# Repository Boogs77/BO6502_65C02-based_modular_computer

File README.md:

# BO6502: 65C02-Based Modular Computer System

Technical overview of the **BO6502** core architecture. This system leverages the iconic 6502 instruction set with modern, high-reliability components from Western Design Center, Atmel, and Hitachi, offering a versatile platform for retro-computing enthusiasts.

### 📖 [Read the operation manual](https://github.com/Boogs77/BO6502-manual) · ▶️ [Try it in the browser emulator](https://boogs77.github.io/BO6502-miniVIC-emulator/)

---

## 🧠 Processing Core & System Control

The system is built around a modular 39-pin bus (36 signals + 3 spares) distributed via a robust backplane.

| Module | Type | Status | Description |
| :--- | :--- | :--- | :--- |
| **[CPU Module](https://github.com/Boogs77/BO6502/tree/main/BO6502%20CPU)** |  |  | Central Processing Unit W65C02S. |
| **[Reset & Clock](https://github.com/Boogs77/BO6502/tree/main/BO6502%20RESET)** |  |  | NE555 Reset and switchable clock (2MHz/1MHz/500kHz). |
| **[Backplate](https://github.com/Boogs77/BO6502/tree/main/BO6502%20BACKPLATE)** |  |  | The 39-pin bus backbone with voltage regulation. |
| **[Bridge Connector](https://github.com/Boogs77/BO6502/tree/main/BO6502%20CONNECTOR)** |  |  | Interconnect for daisy-chaining multiple backplates. |

---

## 💾 Memory Map & Storage

The system features a balanced 64KB memory architecture, divided between high-speed static RAM and non-volatile storage.

### [RAM Module](https://github.com/Boogs77/BO6502/tree/main/BO6502%20RAM) ($0000 - $7FFF)
* **Chip**: HITACHI **HM62256LP-12** (32KB SRAM).
* **Status**: 
* **Features**: Revision 02 includes **8 exclusion jumpers** (J-CS0 to J-CS7) to carve out space for I/O modules. Includes JP4 to bypass system clock triggering.
* **PCB**: [RAM_final_rev02](https://github.com/Boogs77/BO6502/blob/main/BO6502%20RAM/gallery/RAM_final_rev02.png?raw=true).

### [ROM Module](https://github.com/Boogs77/BO6502/tree/main/BO6502%20ROM) ($8000 - $FFFF)
* **Chip**: ATMEL **AT28C256** (32KB EEPROM).
* **Status**: 
* **Features**: Equipped with a **ZIF socket** for easy updates. The "Multi" version uses jumpers (J-CS3, CS4, CS5) to disable ROM in specific ranges for advanced peripherals.
* **PCBs**: [Base](https://github.com/Boogs77/BO6502_65C02-based_modular_computer/blob/main/BO6502%20ROM/gallery/ROM_final_rev01.png?raw=true) | [24K Test](https://github.com/Boogs77/BO6502_65C02-based_modular_computer/blob/main/BO6502%20ROM/gallery/ROM24k_final_rev01.png?raw=true) | [Multi-Selection](https://github.com/Boogs77/BO6502_65C02-based_modular_computer/blob/main/BO6502%20ROM/gallery/ROMmulti_final_rev01.png?raw=true).

---

## 🔌 Peripheral & I/O Addressing

Peripheral addressing is managed via **74LS138** decoders to ensure precise memory mapping and avoid bus contention.

| Module | Type | Status | Address | PCB Link |
| :--- | :--- | :--- | :--- | :--- |
| **[VDU Module](https://github.com/Boogs77/BO6502/tree/main/BO6502%20VDU)** |  |  | **$BXXX** | [VDU PCB](https://github.com/Boogs77/BO6502_65C02-based_modular_computer/blob/main/BO6502%20VDU/gallery/VDU_TMS_final_rev01.png?raw=true) |
| **[Serial I/O](https://github.com/Boogs77/BO6502/tree/main/BO6502%20SERIAL)** |  |  | **$CXXX** | [Serial PCB](https://github.com/Boogs77/BO6502_65C02-based_modular_computer/blob/main/BO6502%20SERIAL/gallery/Serial_final_rev03.png?raw=true) |
| **[SD Card](https://github.com/Boogs77/BO6502/tree/main/BO6502%20SDCard)** |  |  | **$D1BX** | [SD Card PCB](https://github.com/Boogs77/BO6502_65C02-based_modular_computer/blob/main/BO6502%20SDCard/gallery/SDcard_final_rev02%20v2.png?raw=true) |
| **[Standalone Keyb](https://github.com/Boogs77/BO6502/tree/main/BO6502%20KEYb)** |  |  | **$D18X** | [Keyboard PCB](https://github.com/Boogs77/BO6502/blob/main/BO6502%20KEYb/gallery/KEYb_final-rev01.png?raw=true) |
| **[Big LCD Module](https://github.com/Boogs77/BO6502/tree/main/BO6502%20BIGLCD)** |  |  | **$D19X** | [Big LCD Module](https://github.com/Boogs77/BO6502/blob/main/BO6502%20BIGLCD/README.md) |
| **[Legacy LCD/Keyb](https://github.com/Boogs77/BO6502/tree/main/BO6502%20LCD_KEYb)** |  |  | **$DXXX** | [Legacy PCB](https://github.com/Boogs77/BO6502/blob/main/BO6502%20LCD_KEYb/gallery/LCD_KEYb_final_rev02.png?raw=true) |
| **[Sound](BO6502%20AUDIO/README.md)** |  |  | **$D1C0** right, **$D1C4** left | [Sound PCB](BO6502%20AUDIO/export/AUDIO_021.png) |

**Stereo sound**: one PCB with one AY-3-8910, built twice; jumpers J-CS0/J-CS1 select the right or left channel. The left board decodes the address and passes the chip select to the right one on **SPARE2** of the backplane. Details in the [Sound module README](BO6502%20AUDIO/README.md).

---

## 📺 Visual Output Tiers

* **Pro**: **TMS9918A** VDU Module with 32KB dedicated RAM. Supports NTSC Composite Out, Sprites, and 16 Colors.
* **Advanced**: **Toshiba T6963** Graphical LCD (160x128 Pixels).
* **Basic**: **Hitachi HD44780U** 16x2 Character LCD.

---

## 🛠 Diagnostic & Testing Tools

| Module | Type | Status | Function | PCB Link |
| :--- | :--- | :--- | :--- | :--- |
| **[Monitor Interface](https://github.com/Boogs77/BO6502/tree/main/BO6502%20MONITOR)** |  |  | Arduino Mega Bus Sniffer (Ben Eater style). | [Monitor PCB](https://github.com/Boogs77/BO6502/blob/main/BO6502%20MONITOR/gallery/MONITOR_final_rev01.png?raw=true) |
| **[LED Test Board](https://github.com/Boogs77/BO6502/tree/main/BO6502%20LED)** |  |  | Visual 16-LED debug for VIA 65C22 ports. | [LED PCB](https://github.com/Boogs77/BO6502/blob/main/BO6502%20LED/gallery/led_final.png?raw=true) |

---

## 📐 Important Technical Notes

### Jumper Configuration for Advanced Modules
When using the latest system modules (VDU, Joystick, SD Card, etc.), the **ROM** and **RAM** modules must be configured to prevent address conflicts:
- **ROM J-CS3/CS4/CS5**: Set to **VCC** to disable ROM in those specific I/O ranges.
- **SD Card Access**: Provides **Raw Data Access** via bit-banged SPI (PA1=MISO, PA2=MOSI, PA3=SCK, PA4=CS).

## 🎬 Videos

Explanatory videos (about five minutes), in Italian and English, with subtitles. Click a picture to watch the video on YouTube.

**The BO6502 modular computer, module by module**

<table><tr>
<td align="center"><br>Italiano</td>
<td align="center"><br>English</td>
</tr></table>

**The BO6502 sound board and how to program the AY-3-8910**

<table><tr>
<td align="center"><br>Italiano</td>
<td align="center"><br>English</td>
</tr></table>

## 📖 Operation Manual

The **[BO6502 Operation Manual](https://github.com/Boogs77/BO6502-manual)**, in the style of the 1976 Apple-1 manual, describes the system board by board: the 39-pin bus pinout, memory and device maps, address decoding, every module with its jumpers, the schematics and bills of materials, every chip register, the BIOS, WozMon and Microsoft BASIC.

| Language | Screen edition | Print edition |
| :--- | :--- | :--- |
| English | [BO6502_Manual_EN.pdf](https://github.com/Boogs77/BO6502-manual/blob/main/BO6502_Manual_EN.pdf) | [BO6502_Manual_EN_print.pdf](https://github.com/Boogs77/BO6502-manual/blob/main/BO6502_Manual_EN_print.pdf) |
| Italian | [BO6502_Manual_IT.pdf](https://github.com/Boogs77/BO6502-manual/blob/main/BO6502_Manual_IT.pdf) | [BO6502_Manual_IT_print.pdf](https://github.com/Boogs77/BO6502-manual/blob/main/BO6502_Manual_IT_print.pdf) |

## 📜 License

The project is open hardware. You are free to build, use, study, modify and sell it, as long as you credit the author.

| Content | License |
| :--- | :--- |
| **Hardware**: schematics, PCB files, bill of materials | [CERN-OHL-P v2](LICENSE) (permissive) |
| **Documentation and images**: README, photos, renders | [CC BY 4.0](LICENSE-docs) |

Copyright (c) 2026 Boogs77. Please keep the credit "by Boogs77" and a link to this repository in your copies and derivatives.

Third-party code in the firmware (for example Microsoft BASIC and WozMon) is not covered by these licenses.

---

## 🏭 Gerber files

Ready for PCB manufacturing (2 layers, drill file included). The drill hits of each file have been checked against its EAGLE board.

| Gerber (ZIP) | Exported from |
| :--- | :--- |
| [`BO6502_AUDIO_gerber.zip`](BO6502%20AUDIO/export/BO6502_AUDIO_gerber.zip) | `AUDIO_final_rev03.brd` |
| [`BO6502_backplate5V_gerber.zip`](BO6502%20BACKPLATE/export/BO6502_backplate5V_gerber.zip) | `backplate5V_final_rev01.brd` |
| [`BO6502_backplate_gerber.zip`](BO6502%20BACKPLATE/export/BO6502_backplate_gerber.zip) | `backplate_final_rev02.brd` |
| [`BO6502-BigLCD_final_gerber.zip`](BO6502%20BIGLCD/export/BO6502-BigLCD_final_gerber.zip) | `BigLCD_final_rev02.brd` |
| [`BO6502_connector_gerber.zip`](BO6502%20CONNECTOR/export/BO6502_connector_gerber.zip) | `connector_final_rev01.brd` |
| [`BO6502_CPU_gerber.zip`](BO6502%20CPU/export/BO6502_CPU_gerber.zip) | `CPU_final_rev02.brd` |
| [`Joystick_final_rev02_gerber.zip`](BO6502%20JOYSTICK/export/Joystick_final_rev02_gerber.zip) | `Joystick_final_rev02.brd` |
| [`KEYb_final_gerber.zip`](BO6502%20KEYb/export/KEYb_final_gerber.zip) | `KEYb_final-rev01.brd` |
| [`BO6502_LCD-KEYb_gerber.zip`](BO6502%20LCD_KEYb/export/BO6502_LCD-KEYb_gerber.zip) | `LCD_KEYb_final_rev02.brd` |
| [`BO6502_LED_gerber.zip`](BO6502%20LED/export/BO6502_LED_gerber.zip) | `led_final.brd` |
| [`BO6502_MONITOR_gerber.zip`](BO6502%20MONITOR/export/BO6502_MONITOR_gerber.zip) | `MONITOR_final_rev01.brd` |
| [`BO6502-RAM_gerber.zip`](BO6502%20RAM/export/BO6502-RAM_gerber.zip) | `RAM_final_rev02.brd` |
| [`BO6502_reset_gerber.zip`](BO6502%20RESET/export/BO6502_reset_gerber.zip) | `reset_final_rev01.brd` |
| [`BO6502_ROM24K_gerber.zip`](BO6502%20ROM/export/BO6502_ROM24K_gerber.zip) | `ROM24k_final_rev01.brd` |
| [`BO6502_ROM_gerber.zip`](BO6502%20ROM/export/BO6502_ROM_gerber.zip) | `ROM_final_rev01.brd` |
| [`BO6502_ROMMULTI_gerber.zip`](BO6502%20ROM/export/BO6502_ROMMULTI_gerber.zip) | `ROMmulti_final_rev01.brd` |
| [`BO6502_SDCARD_gerber.zip`](BO6502%20SDCard/export/BO6502_SDCARD_gerber.zip) | `SDcard_final_rev02.brd` |
| [`BO6502_serial_gerber.zip`](BO6502%20SERIAL/export/BO6502_serial_gerber.zip) | `Serial_final_rev03.brd` |
| [`VDU_TMS_gerber.zip`](BO6502%20VDU/export/VDU_TMS_gerber.zip) | `VDU_TMS_final_rev01.brd` |

---
© 2026 Boogs77 | BO6502 Project - Technical Documentation.

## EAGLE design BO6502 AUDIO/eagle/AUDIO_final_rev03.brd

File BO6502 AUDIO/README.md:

# BO6502 Sound Module

Sound board for the BO6502 system, built around one **General Instrument AY-3-8910** Programmable Sound Generator (3 voices, noise, envelope).

**One PCB, two channels.** The same board is built twice and the jumpers decide whether it is the **right** or the **left** channel. The idea was to separate the two channels and see whether a single printed design could serve both, saving on PCB production.

| Right channel (red RCA) | Left channel (white RCA) |
| :---: | :---: |
|  |  |

On the right board IC1, IC2 and IC3 are not fitted.

---

## 🔊 Stereo with two boards

| Channel | J-CS0 | J-CS1 | Latch address | Write data | Read data |
| :--- | :---: | :---: | :---: | :---: | :---: |
| **Right** | 2-3 | 2-3 | `$D1C0` | `$D1C1` | `$D1C2` |
| **Left** | 1-2 | 1-2 | `$D1C4` | `$D1C5` | `$D1C6` |

J-CS0 and J-CS1 must always be set to the same channel.

### Shared chip select on SPARE2

The address is decoded **on the left board only**. The resulting chip select (`~CS`, active low) travels to the right board on **SPARE2** (pin 38) of the 39-pin bus.

| Part | Left board | Right board |
| :--- | :---: | :---: |
| IC1, IC2, IC3 (address decoder) | fitted | **not fitted** |
| IC4, IC5 (bus control), IC7 (AY-3-8910) | fitted | fitted |

> [!IMPORTANT]
> * Fit IC1-IC3 on the left board only: otherwise two outputs drive the same SPARE2 line.
> * The right board does not work without the left one on the same bus.
> * Do not use SPARE2 for anything else while the sound boards are plugged in.

---

## 🕹️ Address decoding and bus control

* **IC1, IC2, IC3** (74AC138) decode the range `$D1C0-$D1CF` and generate `~CS`. **A3 is not decoded**, so `$D1C8-$D1CF` repeats `$D1C0-$D1C7`.
* **IC4** (74AC138) combines `~CS`, `A0`, `A1`, `R/~W` and `A2` (channel, through J-CS0 and J-CS1).
* **IC5** (74HCT00) turns the IC4 outputs into `BDIR` and `BC1`. `BC2` is tied to VCC.
* The AY clock is **PHI0** from the bus.

| Offset (from the channel base) | Access | BDIR | BC1 | Operation |
| :---: | :---: | :---: | :---: | :--- |
| +0 | write | 1 | 1 | latch the register number |
| +1 | write | 1 | 0 | write the register |
| +2 | read | 0 | 1 | read the register |

---

## 🎚️ Output and optional amplifier

**Both final boards:** J-CS2 on 1-2, JP1 open (no amplifier), JP2 closed (470 Ω resistor out).

The three AY channels are mixed (R2, R3, R4) to a single **RCA** socket, one per board. An **LM386** amplifier stage was added in case it is needed. The two final boards do not use it.

| Jumper | Setting | Effect |
| :--- | :--- | :--- |
| **J-CS2** | 1-2 | direct output to the RCA socket |
| **J-CS2** | 2-3 | amplified output to the RCA socket |
| **JP1** (AMPLI ON) | closed | feeds the LM386 input |
| **JP2** (R470 OFF) | closed | bypasses the 470 Ω series resistor (R5) of the direct output |
| **JP2** (R470 OFF) | open | R5 in series with the direct output |

The extra jumpers are there to try other configurations according to needs.

---

## 📐 Technical specifications

| Specification | Detail |
| :--- | :--- |
| **Sound chip** | 1x AY-3-8910 per board |
| **Logic** | 4x 74AC138, 1x 74HCT00 (right board: 1x 74AC138, 1x 74HCT00) |
| **Amplifier** | 1x LM386 (optional) |
| **Output** | 1x RCA per board |
| **Bus connector** | 39-pin (36 active + 3 spare, SPARE2 used for `~CS`) |

---

## 📁 Files

| File | Content |
| :--- | :--- |
| [`eagle/AUDIO_final_rev03.sch`](eagle/AUDIO_final_rev03.sch), [`.brd`](eagle/AUDIO_final_rev03.brd) | EAGLE schematic and board, **rev. 03** (final) |
| [`export/BO6502-AUDIO_021.pdf`](export/BO6502-AUDIO_021.pdf) | schematic sheet of rev. 03 (internal file number 021) |
| `eagle/AUDIO_005.*`, `export/BO6502-AUDIO_005.pdf` | superseded version with two AY chips on one board |

---

## 🎬 Video

How the board works and how to program it (4:40, with subtitles). Click a picture to watch it on YouTube.

<table><tr>
<td align="center"><br>Italiano</td>
<td align="center"><br>English</td>
</tr></table>

---

## 📂 Related modules
* 🏗️ **[Backplate System](../BO6502%20BACKPLATE/README.md)**: main bus backbone.
* 🧠 **[CPU Module](../BO6502%20CPU/README.md)**: system processing unit.

---

## 🏭 Gerber files

Ready for PCB manufacturing (2 layers, drill file included). The drill hits of each file have been checked against its EAGLE board.

| Gerber (ZIP) | Exported from |
| :--- | :--- |
| [`BO6502_AUDIO_gerber.zip`](export/BO6502_AUDIO_gerber.zip) | `AUDIO_final_rev03.brd` |

---
© 2026 Boogs77 | Engineered for the 6502 enthusiast.

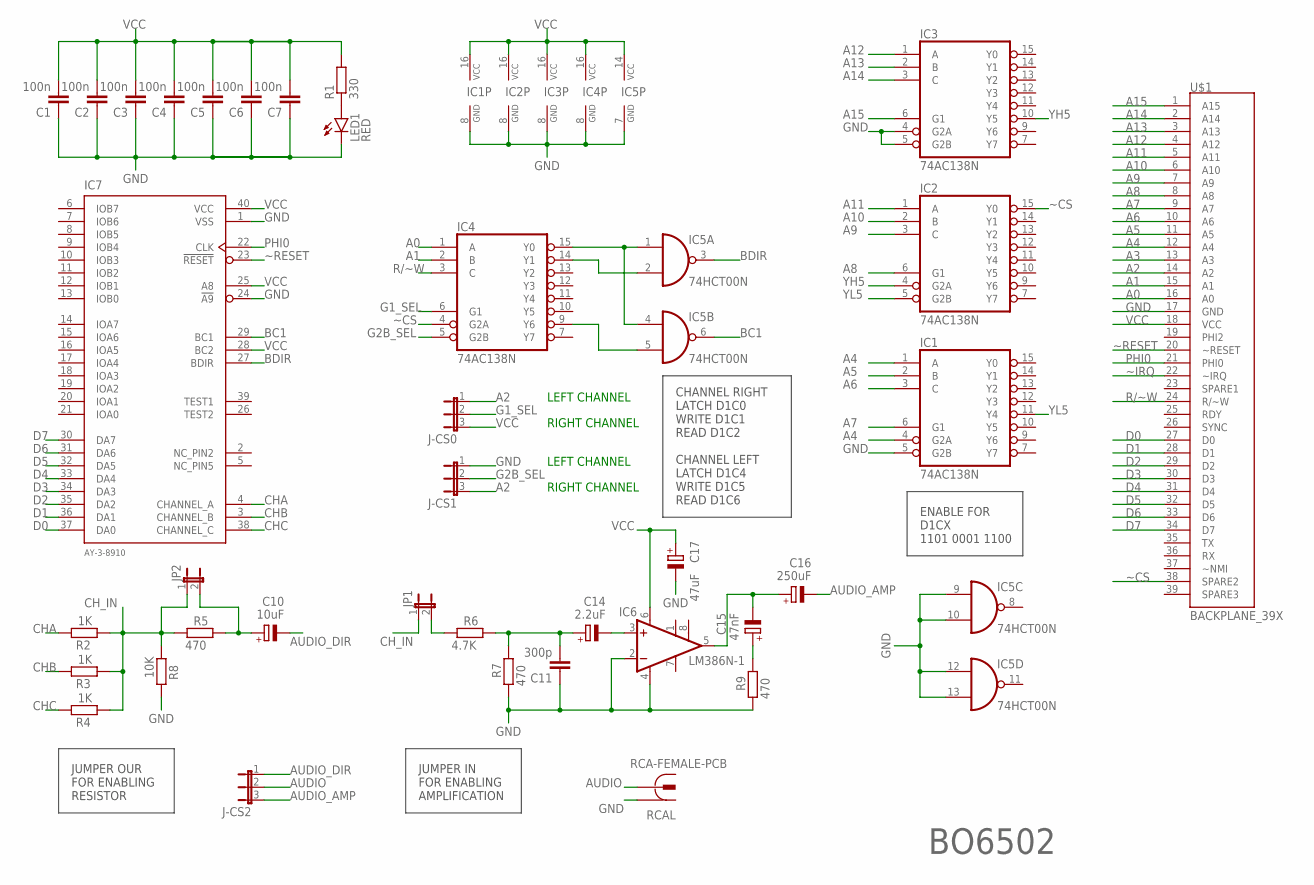
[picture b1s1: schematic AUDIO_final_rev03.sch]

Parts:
C1, C2, C3, C4, C5, C6, C7: 100n; C025-025X050
C10: 10uF; B45181A
C11: 300p; C025-025X050
C14: 2.2uF; B45181A
C15: 47nF; B45181A
C16: 250uF; B45181A
C17: 47uF; B45181A
IC1, IC2, IC3, IC4: 74AC138N; DIL16
IC5: 74HCT00N; DIL14
IC6: LM386N-1; DIL08
IC7: AY-3-8910; DIL40
J-CS0: J-CS0; JP2
J-CS1: J-CS1; JP2
J-CS2: J-CS2; JP2
JP1, JP2: 2PIN; JP1
LED1: RED; LED5MM
R1: 330; 0207/10
R2, R3, R4: 1K; 0207/10
R5, R7, R9: 470; 0207/10
R6: 4.7K; 0207/10
R8: 10K; 0207/10
RCAL: RCA-FEMALE-PCB
U$1: BACKPLANE_39X; BP_39X

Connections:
A0: IC4.1 (A), U$1.16 (A0)
A1: IC4.2 (B), U$1.15 (A1)
A2: J-CS0.1, J-CS1.3, U$1.14 (A2)
A3: U$1.13 (A3)
A4: IC1.1 (A), IC1.4 (G2A), U$1.12 (A4)
A5: IC1.2 (B), U$1.11 (A5)
A6: IC1.3 (C), U$1.10 (A6)
A7: IC1.6 (G1), U$1.9 (A7)
A8: IC2.6 (G1), U$1.8 (A8)
A9: IC2.3 (C), U$1.7 (A9)
A10: IC2.2 (B), U$1.6 (A10)
A11: IC2.1 (A), U$1.5 (A11)
A12: IC3.1 (A), U$1.4 (A12)
A13: IC3.2 (B), U$1.3 (A13)
A14: IC3.3 (C), U$1.2 (A14)
A15: IC3.6 (G1), U$1.1 (A15)
AUDIO: J-CS2.2, RCAL.2@1 (2), RCAL.2@2 (2)
AUDIO_AMP: C16.-, J-CS2.3
AUDIO_DIR: C10.-, J-CS2.1
BC1: IC5.6 (O), IC7.29 (BC1)
BDIR: IC5.3 (O), IC7.27 (BDIR)
CHA: IC7.4 (CHANNEL_A), R2.1
CHB: IC7.3 (CHANNEL_B), R3.1
CHC: IC7.38 (CHANNEL_C), R4.1
CH_IN: JP1.1, JP2.1, R2.2, R3.2, R4.2, R5.2, R8.2
D0: IC7.37 (DA0), U$1.27 (D0)
D1: IC7.36 (DA1), U$1.28 (D1)
D2: IC7.35 (DA2), U$1.29 (D2)
D3: IC7.34 (DA3), U$1.30 (D3)
D4: IC7.33 (DA4), U$1.31 (D4)
D5: IC7.32 (DA5), U$1.32 (D5)
D6: IC7.31 (DA6), U$1.33 (D6)
D7: IC7.30 (DA7), U$1.34 (D7)
G1_SEL: IC4.6 (G1), J-CS0.2
G2B_SEL: IC4.5 (G2B), J-CS1.2
GND: C1.1, C2.1, C3.1, C4.1, C5.1, C6.1, C7.1, C11.1, C17.-, IC1.5 (G2B), IC1.8 (GND), IC2.8 (GND), IC3.4 (G2A), IC3.5 (G2B), IC3.8 (GND), IC4.8 (GND), IC5.7 (GND), IC5.9 (I0), IC5.10 (I1), IC5.12 (I0), IC5.13 (I1), IC6.2 (-IN), IC6.4 (GND), IC7.1 (VSS), IC7.24 (!A9), J-CS1.1, LED1.K (C), R7.2, R8.1, R9.2, RCAL.1, U$1.17 (GND)
unnamed: JP1.2, R6.2
unnamed: IC4.15 (Y0), IC5.1 (I0), IC5.4 (I0)
unnamed: C14.-, IC6.3 (+IN)
unnamed: IC4.14 (Y1), IC5.2 (I1)
unnamed: LED1.A, R1.1
unnamed: C10.+, JP2.2, R5.1
unnamed: IC4.9 (Y6), IC5.5 (I1)
unnamed: C11.2, C14.+, R6.1, R7.1
unnamed: C15.-, C16.+, IC6.5 (OUT)
unnamed: C15.+, R9.1
PHI0: IC7.22 (CLK), U$1.21 (PHI0)
R/~W: IC4.3 (C), U$1.24 (R/~W)
VCC: C1.2, C2.2, C3.2, C4.2, C5.2, C6.2, C7.2, C17.+, IC1.16 (VCC), IC2.16 (VCC), IC3.16 (VCC), IC4.16 (VCC), IC5.14 (VCC), IC6.6 (VS), IC7.25 (A8), IC7.28 (BC2), IC7.40 (VCC), J-CS0.3, R1.2, U$1.18 (VCC)
YH5: IC2.4 (G2A), IC3.10 (Y5)
YL5: IC1.11 (Y4), IC2.5 (G2B)
~CS: IC2.15 (Y0), IC4.4 (G2A), U$1.38 (SPARE2)
~IRQ: U$1.22 (~IRQ)
~RESET: IC7.23 (!RESET), U$1.20 (~RESET)

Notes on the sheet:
BO6502
ENABLE FOR D1CX 1101 0001 1100
LEFT CHANNEL
RIGHT CHANNEL
JUMPER OUR FOR ENABLING RESISTOR
JUMPER IN FOR ENABLING AMPLIFICATION
CHANNEL RIGHT LATCH D1C0 WRITE D1C1 READ D1C2 CHANNEL LEFT LATCH D1C4 WRITE D1C5 READ D1C6

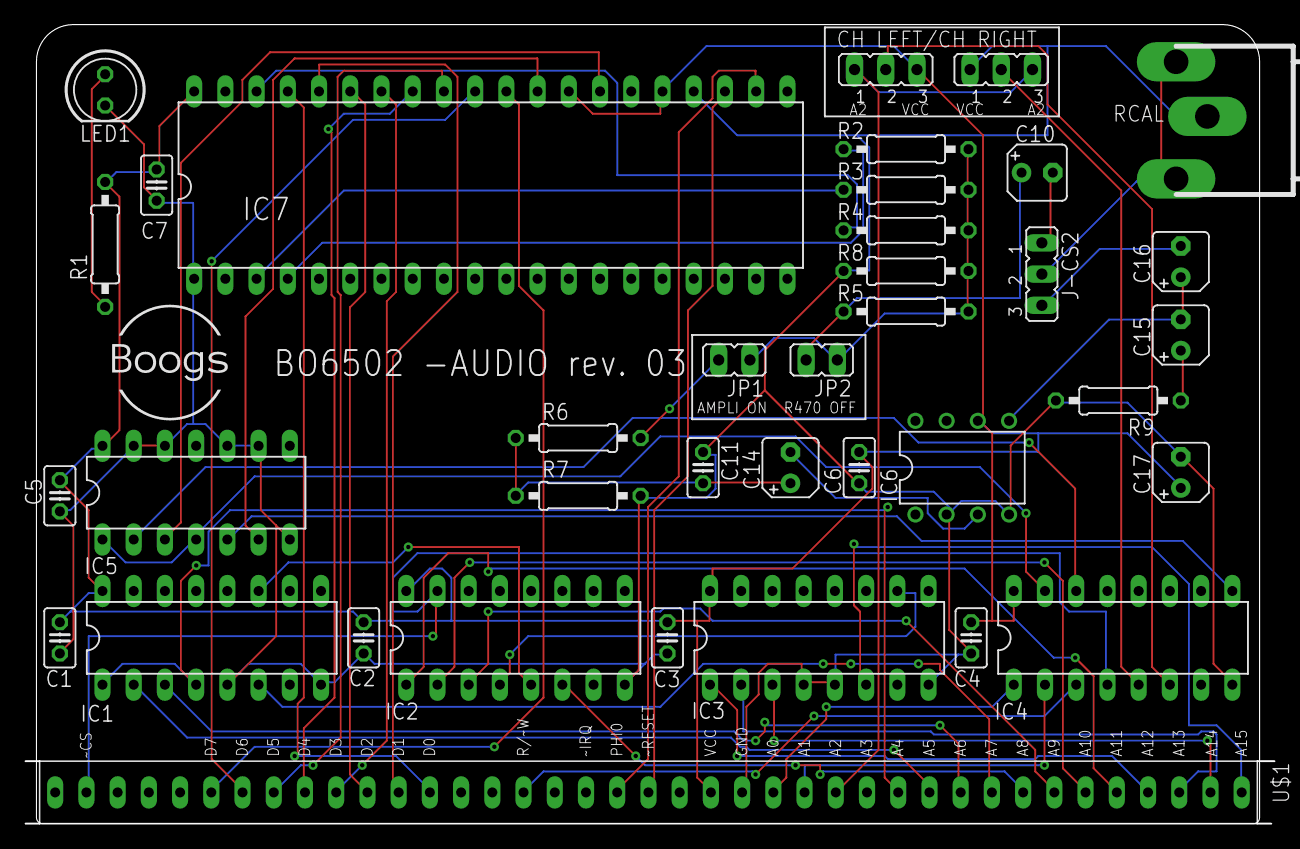
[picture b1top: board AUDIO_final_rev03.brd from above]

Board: 2 copper layers, 101.6 x 65.0 mm, 37 parts (0 on the bottom side), 52 nets.

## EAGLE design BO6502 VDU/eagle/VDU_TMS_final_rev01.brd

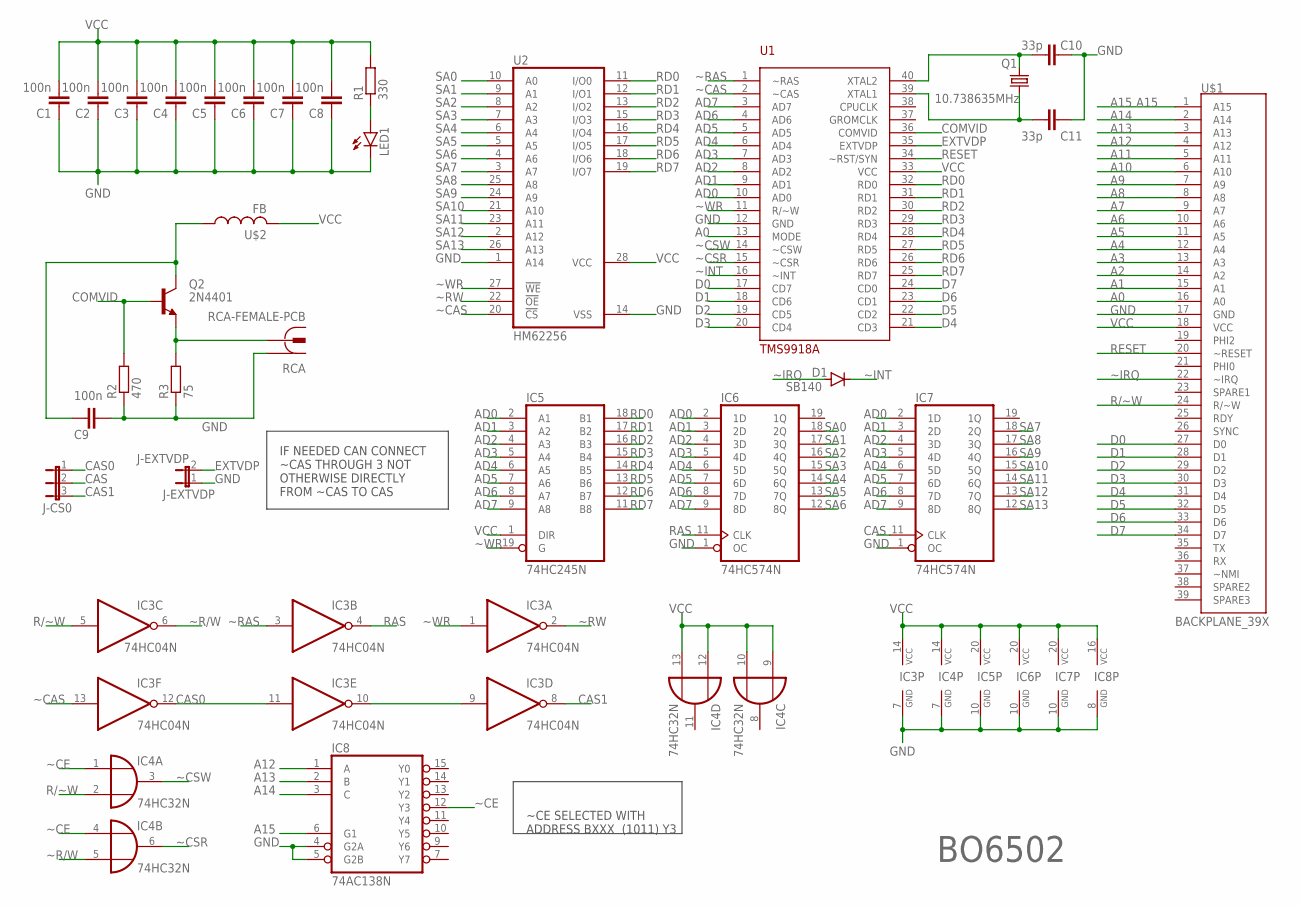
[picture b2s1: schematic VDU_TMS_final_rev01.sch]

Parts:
C1, C2, C3, C4, C5, C6, C7, C8, C9: 100n; C025-025X050
C10, C11: 33p; C025-025X050
D1: SB140; DO41-10
IC3: 74HC04N; DIL14
IC4: 74HC32N; DIL14
IC5: 74HC245N; DIL20
IC6, IC7: 74HC574N; DIL20
IC8: 74AC138N; DIL16
J-CAS: J-CS0; JP2
J-EXTVDP: J-EXTVDP; JP1
LED1: RED; LED5MM
Q1: 10.738635MHz; HC49/S
Q2: 2N4401; TO92-EBC
R1: 330; 0207/10
R2: 470; 0207/10
R3: 75; 0207/10
RCA: RCA-FEMALE-PCB
U1: TMS9918A; DIL40
U2: HM62256; DIL28-6
U$1: BACKPLANE_39X; BP_39X
U$2: FB

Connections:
A0: U1.13 (MODE), U$1.16 (A0)
A1: U$1.15 (A1)
A2: U$1.14 (A2)
A3: U$1.13 (A3)
A4: U$1.12 (A4)
A5: U$1.11 (A5)
A6: U$1.10 (A6)
A7: U$1.9 (A7)
A8: U$1.8 (A8)
A9: U$1.7 (A9)
A10: U$1.6 (A10)
A11: U$1.5 (A11)
A12: IC8.1 (A), U$1.4 (A12)
A13: IC8.2 (B), U$1.3 (A13)
A14: IC8.3 (C), U$1.2 (A14)
A15: IC8.6 (G1), U$1.1 (A15)
AD0: IC5.2 (A1), IC6.2 (1D), IC7.2 (1D), U1.10 (AD0)
AD1: IC5.3 (A2), IC6.3 (2D), IC7.3 (2D), U1.9 (AD1)
AD2: IC5.4 (A3), IC6.4 (3D), IC7.4 (3D), U1.8 (AD2)
AD3: IC5.5 (A4), IC6.5 (4D), IC7.5 (4D), U1.7 (AD3)
AD4: IC5.6 (A5), IC6.6 (5D), IC7.6 (5D), U1.6 (AD4)
AD5: IC5.7 (A6), IC6.7 (6D), IC7.7 (6D), U1.5 (AD5)
AD6: IC5.8 (A7), IC6.8 (7D), IC7.8 (7D), U1.4 (AD6)
AD7: IC5.9 (A8), IC6.9 (8D), IC7.9 (8D), U1.3 (AD7)
CAS: IC7.11 (CLK), J-CAS.2
CAS0: IC3.11 (I), IC3.12 (O), J-CAS.1
CAS1: IC3.8 (O), J-CAS.3
COMVID: Q2.B, R2.2, U1.36 (COMVID)
D0: U1.17 (CD7), U$1.27 (D0)
D1: U1.18 (CD6), U$1.28 (D1)
D2: U1.19 (CD5), U$1.29 (D2)
D3: U1.20 (CD4), U$1.30 (D3)
D4: U1.21 (CD3), U$1.31 (D4)
D5: U1.22 (CD2), U$1.32 (D5)
D6: U1.23 (CD1), U$1.33 (D6)
D7: U1.24 (CD0), U$1.34 (D7)
EXTVDP: J-EXTVDP.2, U1.35 (EXTVDP)
GND: C1.1, C2.1, C3.1, C4.1, C5.1, C6.1, C7.1, C8.1, C9.1, C10.1, C11.1, IC3.7 (GND), IC4.7 (GND), IC5.10 (GND), IC6.1 (OC), IC6.10 (GND), IC7.1 (OC), IC7.10 (GND), IC8.4 (G2A), IC8.5 (G2B), IC8.8 (GND), J-EXTVDP.1, LED1.K (C), R2.1, R3.1, RCA.1, U1.12 (GND), U2.1 (A14), U2.14 (VSS), U$1.17 (GND)
unnamed: Q2.E, R3.2, RCA.2@1 (2), RCA.2@2 (2)
unnamed: C9.2, Q2.C, U$2.P$1 (1)
unnamed: C10.2, Q1.2, U1.40 (XTAL2)
unnamed: LED1.A, R1.1
unnamed: C11.2, Q1.1, U1.39 (XTAL1)
unnamed: IC3.9 (I), IC3.10 (O)
R/~W: IC3.5 (I), IC4.2 (I1), U$1.24 (R/~W)
RAS: IC3.4 (O), IC6.11 (CLK)
RD0: IC5.18 (B1), U1.32 (RD0), U2.11 (I/O0)
RD1: IC5.17 (B2), U1.31 (RD1), U2.12 (I/O1)
RD2: IC5.16 (B3), U1.30 (RD2), U2.13 (I/O2)
RD3: IC5.15 (B4), U1.29 (RD3), U2.15 (I/O3)
RD4: IC5.14 (B5), U1.28 (RD4), U2.16 (I/O4)
RD5: IC5.13 (B6), U1.27 (RD5), U2.17 (I/O5)
RD6: IC5.12 (B7), U1.26 (RD6), U2.18 (I/O6)
RD7: IC5.11 (B8), U1.25 (RD7), U2.19 (I/O7)
RESET: U1.34 (~RST/SYN), U$1.20 (~RESET)
SA0: IC6.18 (2Q), U2.10 (A0)
SA1: IC6.17 (3Q), U2.9 (A1)
SA2: IC6.16 (4Q), U2.8 (A2)
SA3: IC6.15 (5Q), U2.7 (A3)
SA4: IC6.14 (6Q), U2.6 (A4)
SA5: IC6.13 (7Q), U2.5 (A5)
SA6: IC6.12 (8Q), U2.4 (A6)
SA7: IC7.18 (2Q), U2.3 (A7)
SA8: IC7.17 (3Q), U2.25 (A8)
SA9: IC7.16 (4Q), U2.24 (A9)
SA10: IC7.15 (5Q), U2.21 (A10)
SA11: IC7.14 (6Q), U2.23 (A11)
SA12: IC7.13 (7Q), U2.2 (A12)
SA13: IC7.12 (8Q), U2.26 (A13)
VCC: C1.2, C2.2, C3.2, C4.2, C5.2, C6.2, C7.2, C8.2, IC3.14 (VCC), IC4.9 (I0), IC4.10 (I1), IC4.12 (I0), IC4.13 (I1), IC4.14 (VCC), IC5.1 (DIR), IC5.20 (VCC), IC6.20 (VCC), IC7.20 (VCC), IC8.16 (VCC), R1.2, U1.33 (VCC), U2.28 (VCC), U$1.18 (VCC), U$2.P$2 (2)
~CAS: IC3.13 (I), U1.2 (~CAS), U2.20 (!CS)
~CE: IC4.1 (I0), IC4.4 (I0), IC8.12 (Y3)
~CSR: IC4.6 (O), U1.15 (~CSR)
~CSW: IC4.3 (O), U1.14 (~CSW)
~INT: D1.C, U1.16 (~INT)
~IRQ: D1.A, U$1.22 (~IRQ)
~R/W: IC3.6 (O), IC4.5 (I1)
~RAS: IC3.3 (I), U1.1 (~RAS)
~RW: IC3.2 (O), U2.22 (!OE)
~WR: IC3.1 (I), IC5.19 (G), U1.11 (R/~W), U2.27 (!WE)

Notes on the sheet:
BO6502
IF NEEDED CAN CONNECT ~CAS THROUGH 3 NOT OTHERWISE DIRECTLY FROM ~CAS TO CAS
~CE SELECTED WITH ADDRESS BXXX (1011) Y3

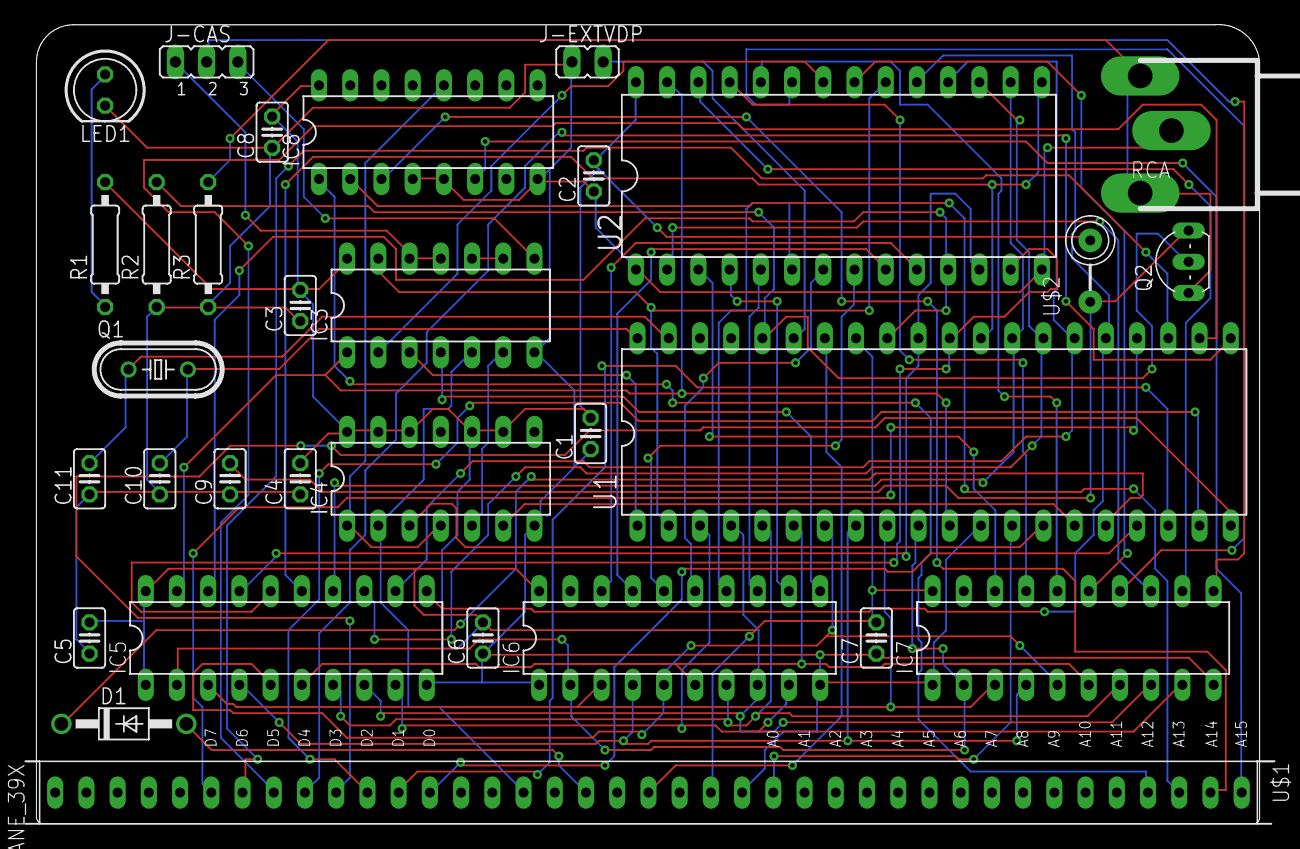
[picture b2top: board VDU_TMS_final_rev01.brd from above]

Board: 2 copper layers, 101.6 x 65.0 mm, 31 parts (0 on the bottom side), 69 nets.

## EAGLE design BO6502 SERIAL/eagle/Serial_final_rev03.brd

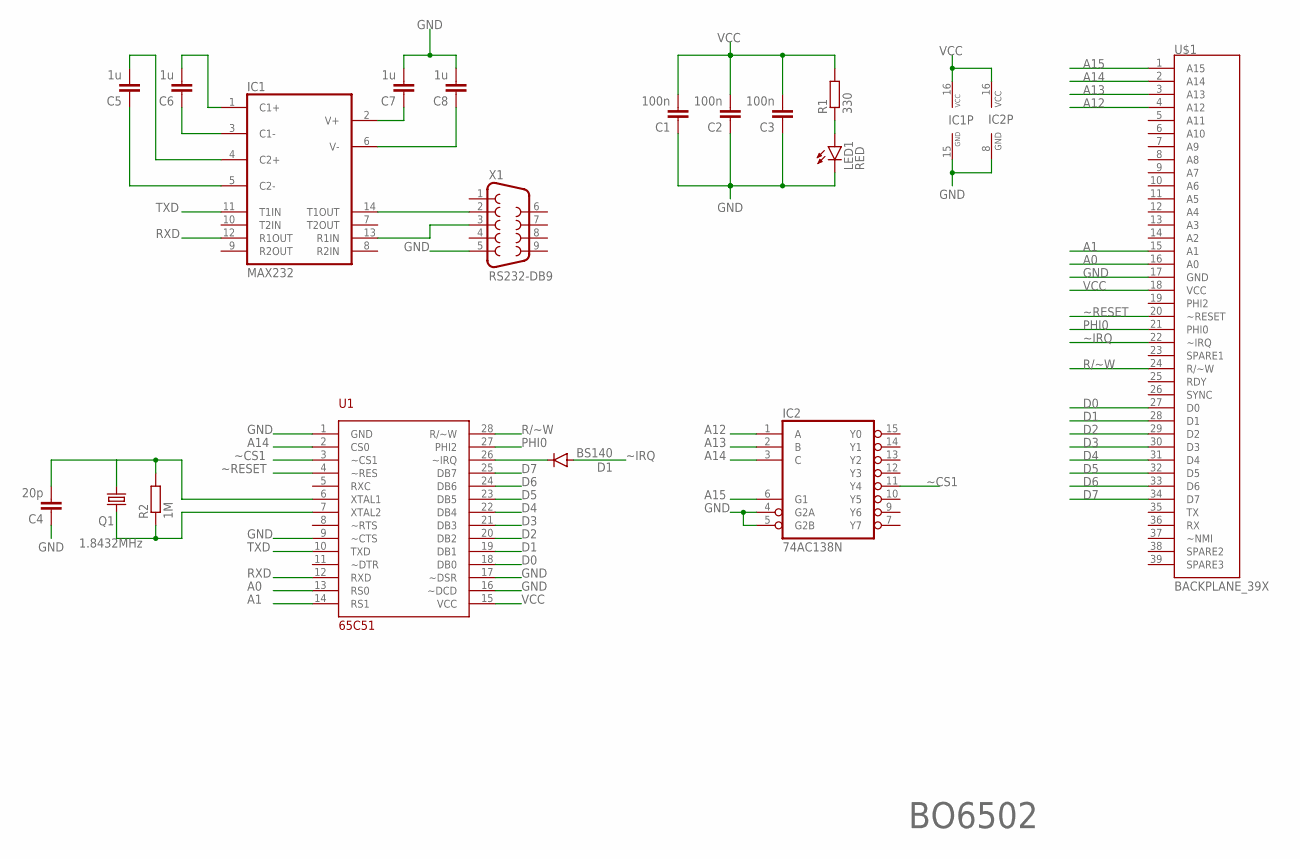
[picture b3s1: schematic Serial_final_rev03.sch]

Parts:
C1, C2, C3: 100n; C025-025X050
C4: 20p; C025-025X050
C5, C6, C7, C8: 1u; C050-025X075
D1: BS140; DO41-10
IC1: MAX232; DIL16
IC2: 74AC138N; DIL16
LED1: RED; LED5MM
Q1: 1.8432MHz; HC49/S
R1: 330; 0207/10
R2: 1M; 0207/10
U1: 65C51; DIL28
U$1: BACKPLANE_39X; BP_39X
X1: RS232-DB9; F09HP

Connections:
A0: U1.13 (RS0), U$1.16 (A0)
A1: U1.14 (RS1), U$1.15 (A1)
A12: IC2.1 (A), U$1.4 (A12)
A13: IC2.2 (B), U$1.3 (A13)
A14: IC2.3 (C), U1.2 (CS0), U$1.2 (A14)
A15: IC2.6 (G1), U$1.1 (A15)
D0: U1.18 (DB0), U$1.27 (D0)
D1: U1.19 (DB1), U$1.28 (D1)
D2: U1.20 (DB2), U$1.29 (D2)
D3: U1.21 (DB3), U$1.30 (D3)
D4: U1.22 (DB4), U$1.31 (D4)
D5: U1.23 (DB5), U$1.32 (D5)
D6: U1.24 (DB6), U$1.33 (D6)
D7: U1.25 (DB7), U$1.34 (D7)
GND: C1.1, C2.1, C3.1, C4.1, C7.2, C8.2, IC1.15 (GND), IC2.4 (G2A), IC2.5 (G2B), IC2.8 (GND), LED1.K (C), U1.1 (GND), U1.9 (~CTS), U1.16 (~DCD), U1.17 (~DSR), U$1.17 (GND), X1.5
unnamed: C6.2, IC1.1 (C1+)
unnamed: D1.C, U1.26 (~IRQ)
unnamed: C6.1, IC1.3 (C1-)
unnamed: C5.2, IC1.4 (C2+)
unnamed: C5.1, IC1.5 (C2-)
unnamed: LED1.A, R1.1
unnamed: IC1.14 (T1OUT), X1.2
unnamed: IC1.13 (R1IN), X1.3
unnamed: C7.1, IC1.2 (V+)
unnamed: C8.1, IC1.6 (V-)
unnamed: C4.2, Q1.2, R2.2, U1.6 (XTAL1)
unnamed: Q1.1, R2.1, U1.7 (XTAL2)
PHI0: U1.27 (PHI2), U$1.21 (PHI0)
R/~W: U1.28 (R/~W), U$1.24 (R/~W)
RXD: IC1.12 (R1OUT), U1.12 (RXD)
TXD: IC1.11 (T1IN), U1.10 (TXD)
VCC: C1.2, C2.2, C3.2, IC1.16 (VCC), IC2.16 (VCC), R1.2, U1.15 (VCC), U$1.18 (VCC)
~CS1: IC2.11 (Y4), U1.3 (~CS1)
~IRQ: D1.A, U$1.22 (~IRQ)
~RESET: U1.4 (~RES), U$1.20 (~RESET)

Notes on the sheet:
BO6502

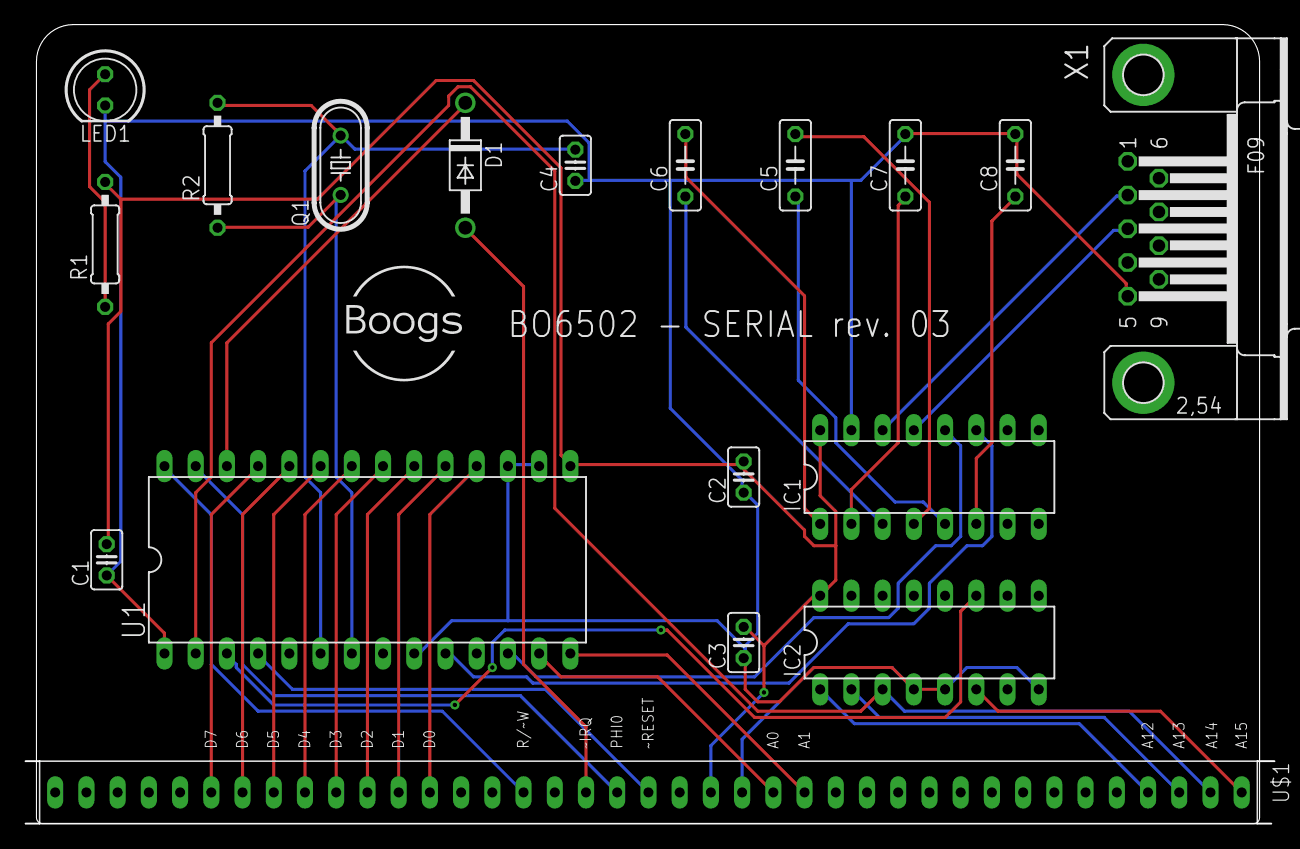
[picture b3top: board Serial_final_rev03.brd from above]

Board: 2 copper layers, 101.6 x 65.0 mm, 18 parts (0 on the bottom side), 35 nets.

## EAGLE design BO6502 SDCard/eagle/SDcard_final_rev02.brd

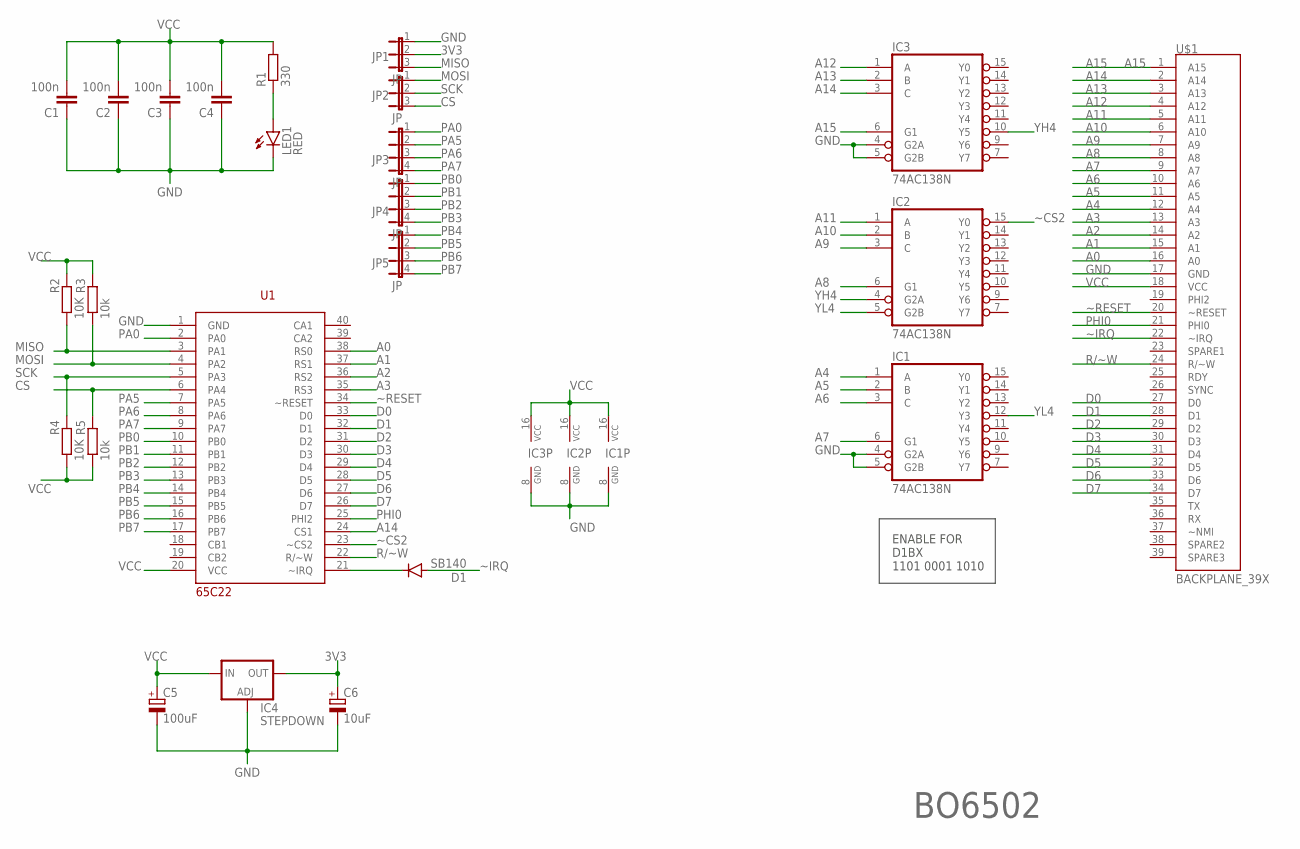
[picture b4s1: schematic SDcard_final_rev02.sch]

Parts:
C1, C2, C3, C4: 100n; C025-025X050
C5: 100uF; B45181A
C6: 10uF; B45181A
D1: SB140; DO41-10
IC1, IC2, IC3: 74AC138N; DIL16
IC4: STEPDOWN; 317TS
JP1, JP2: JP; JP2
JP3, JP4, JP5: JP; JP4
LED1: RED; LED5MM
R1: 330; 0207/10
R2, R4: 10K; 0207/10
R3, R5: 10k; 0207/10
U1: 65C22; DIL40
U$1: BACKPLANE_39X; BP_39X

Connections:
3V3: C6.+, IC4.2 (OUT), JP1.2
A0: U1.38 (RS0), U$1.16 (A0)
A1: U1.37 (RS1), U$1.15 (A1)
A2: U1.36 (RS2), U$1.14 (A2)
A3: U1.35 (RS3), U$1.13 (A3)
A4: IC1.1 (A), U$1.12 (A4)
A5: IC1.2 (B), U$1.11 (A5)
A6: IC1.3 (C), U$1.10 (A6)
A7: IC1.6 (G1), U$1.9 (A7)
A8: IC2.6 (G1), U$1.8 (A8)
A9: IC2.3 (C), U$1.7 (A9)
A10: IC2.2 (B), U$1.6 (A10)
A11: IC2.1 (A), U$1.5 (A11)
A12: IC3.1 (A), U$1.4 (A12)
A13: IC3.2 (B), U$1.3 (A13)
A14: IC3.3 (C), U1.24 (CS1), U$1.2 (A14)
A15: IC3.6 (G1), U$1.1 (A15)
CS: JP2.3, R5.2, U1.6 (PA4)
D0: U1.33 (D0), U$1.27 (D0)
D1: U1.32 (D1), U$1.28 (D1)
D2: U1.31 (D2), U$1.29 (D2)
D3: U1.30 (D3), U$1.30 (D3)
D4: U1.29 (D4), U$1.31 (D4)
D5: U1.28 (D5), U$1.32 (D5)
D6: U1.27 (D6), U$1.33 (D6)
D7: U1.26 (D7), U$1.34 (D7)
GND: C1.1, C2.1, C3.1, C4.1, C5.-, C6.-, IC1.4 (G2A), IC1.5 (G2B), IC1.8 (GND), IC2.8 (GND), IC3.4 (G2A), IC3.5 (G2B), IC3.8 (GND), IC4.1 (ADJ), JP1.1, LED1.K (C), U1.1 (GND), U$1.17 (GND)
MISO: JP1.3, R2.1, U1.3 (PA1)
MOSI: JP2.1, R3.1, U1.4 (PA2)
unnamed: D1.C, U1.21 (~IRQ)
unnamed: LED1.A, R1.1
PA0: JP3.1, U1.2 (PA0)
PA5: JP3.2, U1.7 (PA5)
PA6: JP3.3, U1.8 (PA6)
PA7: JP3.4, U1.9 (PA7)
PB0: JP4.1, U1.10 (PB0)
PB1: JP4.2, U1.11 (PB1)
PB2: JP4.3, U1.12 (PB2)
PB3: JP4.4, U1.13 (PB3)
PB4: JP5.1, U1.14 (PB4)
PB5: JP5.2, U1.15 (PB5)
PB6: JP5.3, U1.16 (PB6)
PB7: JP5.4, U1.17 (PB7)
PHI0: U1.25 (PHI2), U$1.21 (PHI0)
R/~W: U1.22 (R/~W), U$1.24 (R/~W)
SCK: JP2.2, R4.2, U1.5 (PA3)
VCC: C1.2, C2.2, C3.2, C4.2, C5.+, IC1.16 (VCC), IC2.16 (VCC), IC3.16 (VCC), IC4.3 (IN), R1.2, R2.2, R3.2, R4.1, R5.1, U1.20 (VCC), U$1.18 (VCC)
YH4: IC2.4 (G2A), IC3.10 (Y5)
YL4: IC1.12 (Y3), IC2.5 (G2B)
~CS2: IC2.15 (Y0), U1.23 (~CS2)
~IRQ: D1.A, U$1.22 (~IRQ)
~RESET: U1.34 (~RESET), U$1.20 (~RESET)

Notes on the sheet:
BO6502
ENABLE FOR D1BX 1101 0001 1010

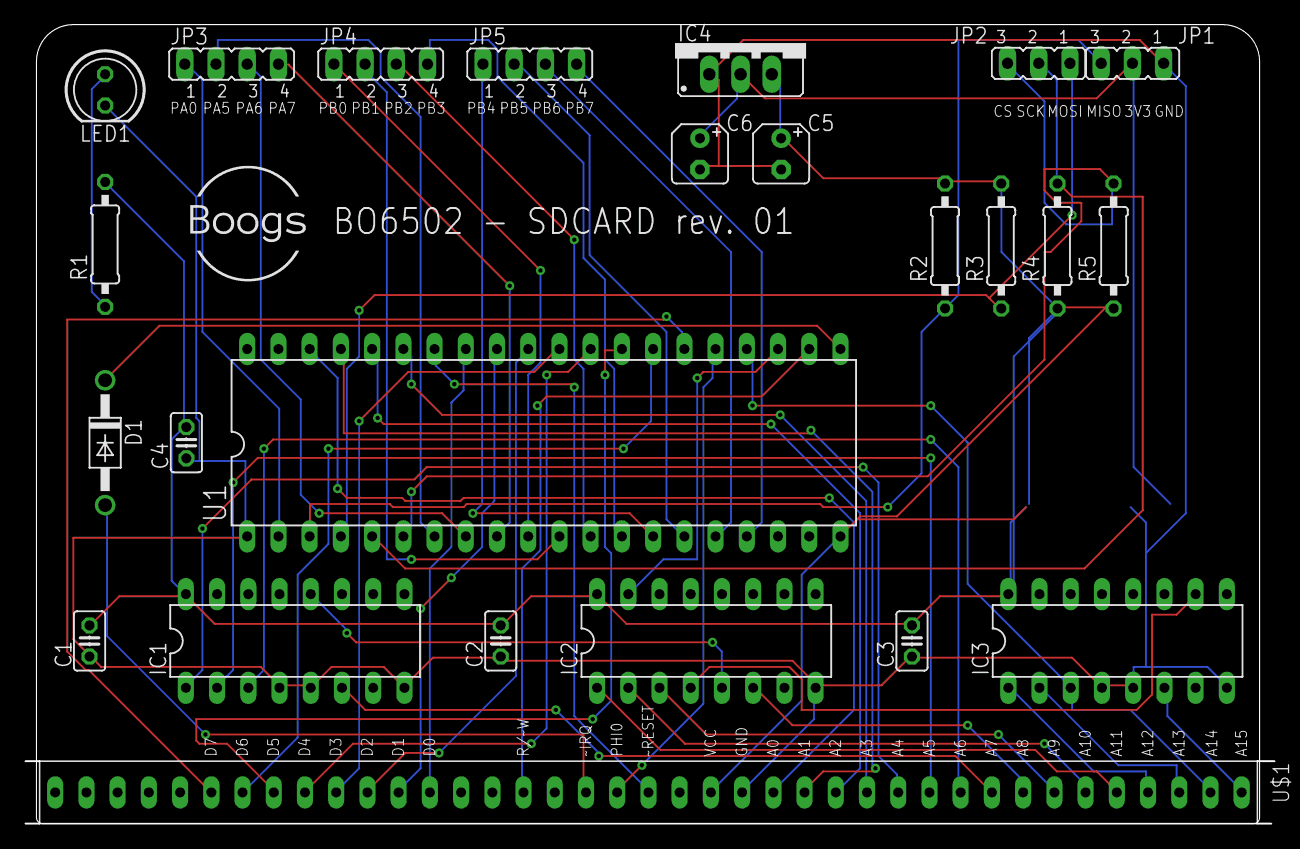
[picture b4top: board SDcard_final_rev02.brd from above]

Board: 2 copper layers, 101.6 x 65.0 mm, 24 parts (0 on the bottom side), 52 nets.

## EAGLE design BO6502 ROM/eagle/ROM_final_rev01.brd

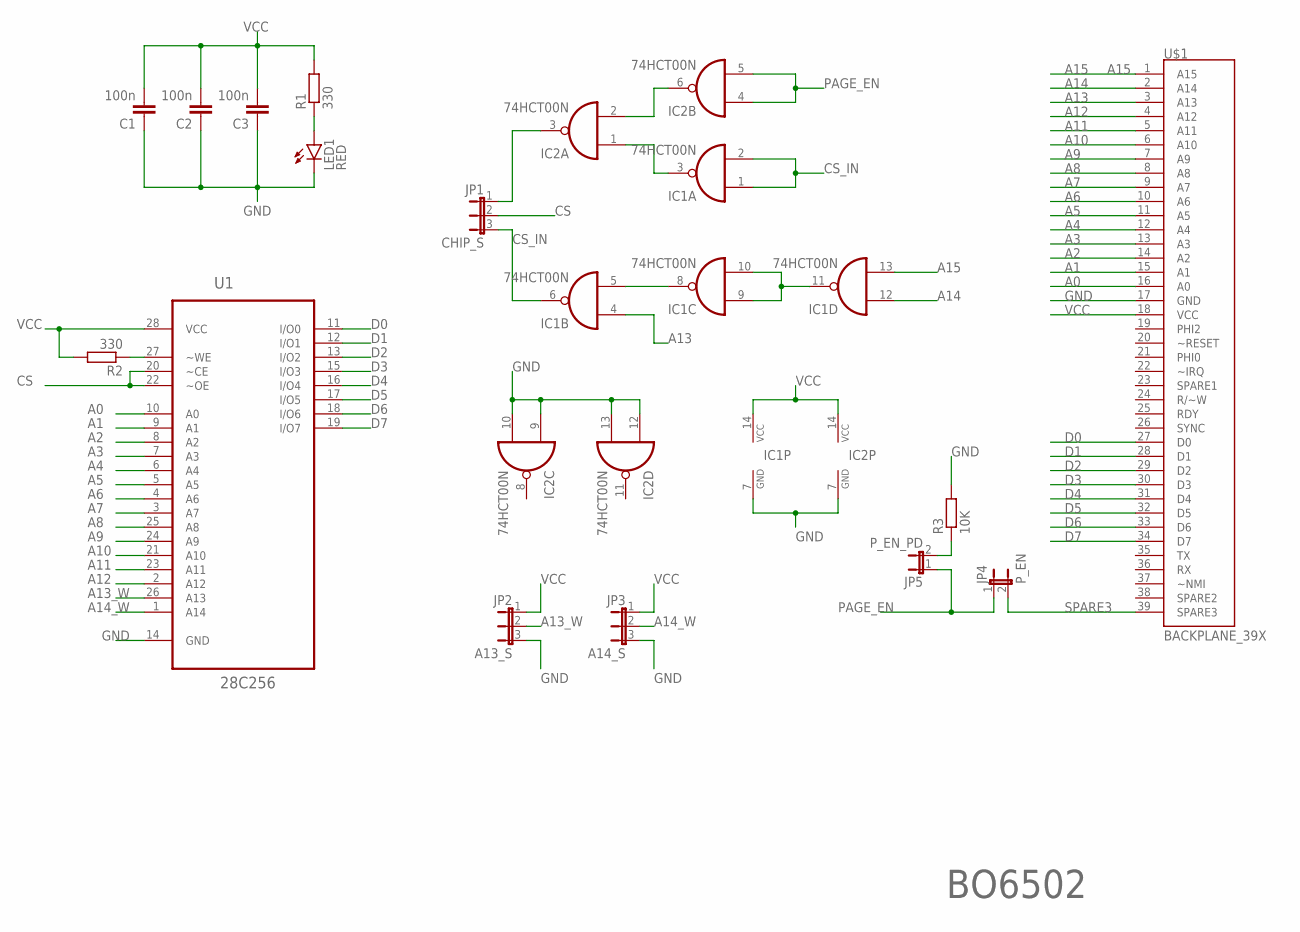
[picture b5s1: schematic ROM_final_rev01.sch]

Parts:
C1, C2, C3: 100n; C025-025X050
IC1, IC2: 74HCT00N; DIL14
JP1: CHIP_S; JP2
JP2: A13_S; JP2
JP3: A14_S; JP2
JP4: P_EN; JP1
JP5: P_EN_PD; JP1
LED1: RED; LED5MM
R1, R2: 330; 0207/10
R3: 10K; 0207/10
U1: 28C256; DIP254P1524X482-28
U$1: BACKPLANE_39X; BP_39X

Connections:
A0: U1.10 (A0), U$1.16 (A0)
A1: U1.9 (A1), U$1.15 (A1)
A2: U1.8 (A2), U$1.14 (A2)
A3: U1.7 (A3), U$1.13 (A3)
A4: U1.6 (A4), U$1.12 (A4)
A5: U1.5 (A5), U$1.11 (A5)
A6: U1.4 (A6), U$1.10 (A6)
A7: U1.3 (A7), U$1.9 (A7)
A8: U1.25 (A8), U$1.8 (A8)
A9: U1.24 (A9), U$1.7 (A9)
A10: U1.21 (A10), U$1.6 (A10)
A11: U1.23 (A11), U$1.5 (A11)
A12: U1.2 (A12), U$1.4 (A12)
A13: IC1.4 (I0), U$1.3 (A13)
A13_W: JP2.2, U1.26 (A13)
A14: IC1.12 (I0), U$1.2 (A14)
A14_W: JP3.2, U1.1 (A14)
A15: IC1.13 (I1), U$1.1 (A15)
CS: JP1.2, U1.20 (~CE), U1.22 (~OE)
CS_IN: IC1.1 (I0), IC1.2 (I1), IC1.6 (O), JP1.3
D0: U1.11 (I/O0), U$1.27 (D0)
D1: U1.12 (I/O1), U$1.28 (D1)
D2: U1.13 (I/O2), U$1.29 (D2)
D3: U1.15 (I/O3), U$1.30 (D3)
D4: U1.16 (I/O4), U$1.31 (D4)
D5: U1.17 (I/O5), U$1.32 (D5)
D6: U1.18 (I/O6), U$1.33 (D6)
D7: U1.19 (I/O7), U$1.34 (D7)
GND: C1.1, C2.1, C3.1, IC1.7 (GND), IC2.7 (GND), IC2.9 (I0), IC2.10 (I1), IC2.12 (I0), IC2.13 (I1), JP2.3, JP3.3, LED1.K (C), R3.2, U1.14 (GND), U$1.17 (GND)
unnamed: R2.1, U1.27 (~WE)
unnamed: IC2.2 (I1), IC2.6 (O)
unnamed: IC1.3 (O), IC2.1 (I0)
unnamed: IC2.3 (O), JP1.1
unnamed: IC1.5 (I1), IC1.8 (O)
unnamed: LED1.A, R1.1
unnamed: IC1.9 (I0), IC1.10 (I1), IC1.11 (O)
unnamed: JP5.2, R3.1
PAGE_EN: IC2.4 (I0), IC2.5 (I1), JP4.1, JP5.1
SPARE3: JP4.2, U$1.39 (SPARE3)
VCC: C1.2, C2.2, C3.2, IC1.14 (VCC), IC2.14 (VCC), JP2.1, JP3.1, R1.2, R2.2, U1.28 (VCC), U$1.18 (VCC)

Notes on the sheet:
BO6502

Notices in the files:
parts and their libraries:
SparkFun-Switches: Licensing: Creative Commons ShareAlike 4.0 International - https://creativecommons.org/licenses/by-sa/4.0
